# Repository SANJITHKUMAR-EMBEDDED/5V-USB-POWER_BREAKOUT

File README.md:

# USB-C to 3.3V Power Supply

A simple and robust power supply board that takes 5V from any USB-C port and provides a stable 3.3V output. This is **Project 1** of my #50BoardChallenge to become a job-ready PCB design engineer.

## Features
* USB-C Power Input
* 3.3V LDO Regulator (AP2112K)
* Header pin outputs for both 5V and 3.3V
* 4x 3mm Mounting Holes for stable mounting

## Professional Design Rules
This board was designed using a professional workflow in KiCad:
* **Solid `GND` Plane:** Used a solid copper pour on the bottom layer for low noise and a stable return path.
* **Power Traces:** Used KiCad's **Net Classes** to define wide `20mil` traces for the `+5V`, `+3.3V`, and `GND` nets.
* **Decoupling:** Placed input and output capacitors as close as possible to the regulator for stability.
* **DRC:** The final design passed all Design Rules Checks with **0 errors and 0 warnings**.

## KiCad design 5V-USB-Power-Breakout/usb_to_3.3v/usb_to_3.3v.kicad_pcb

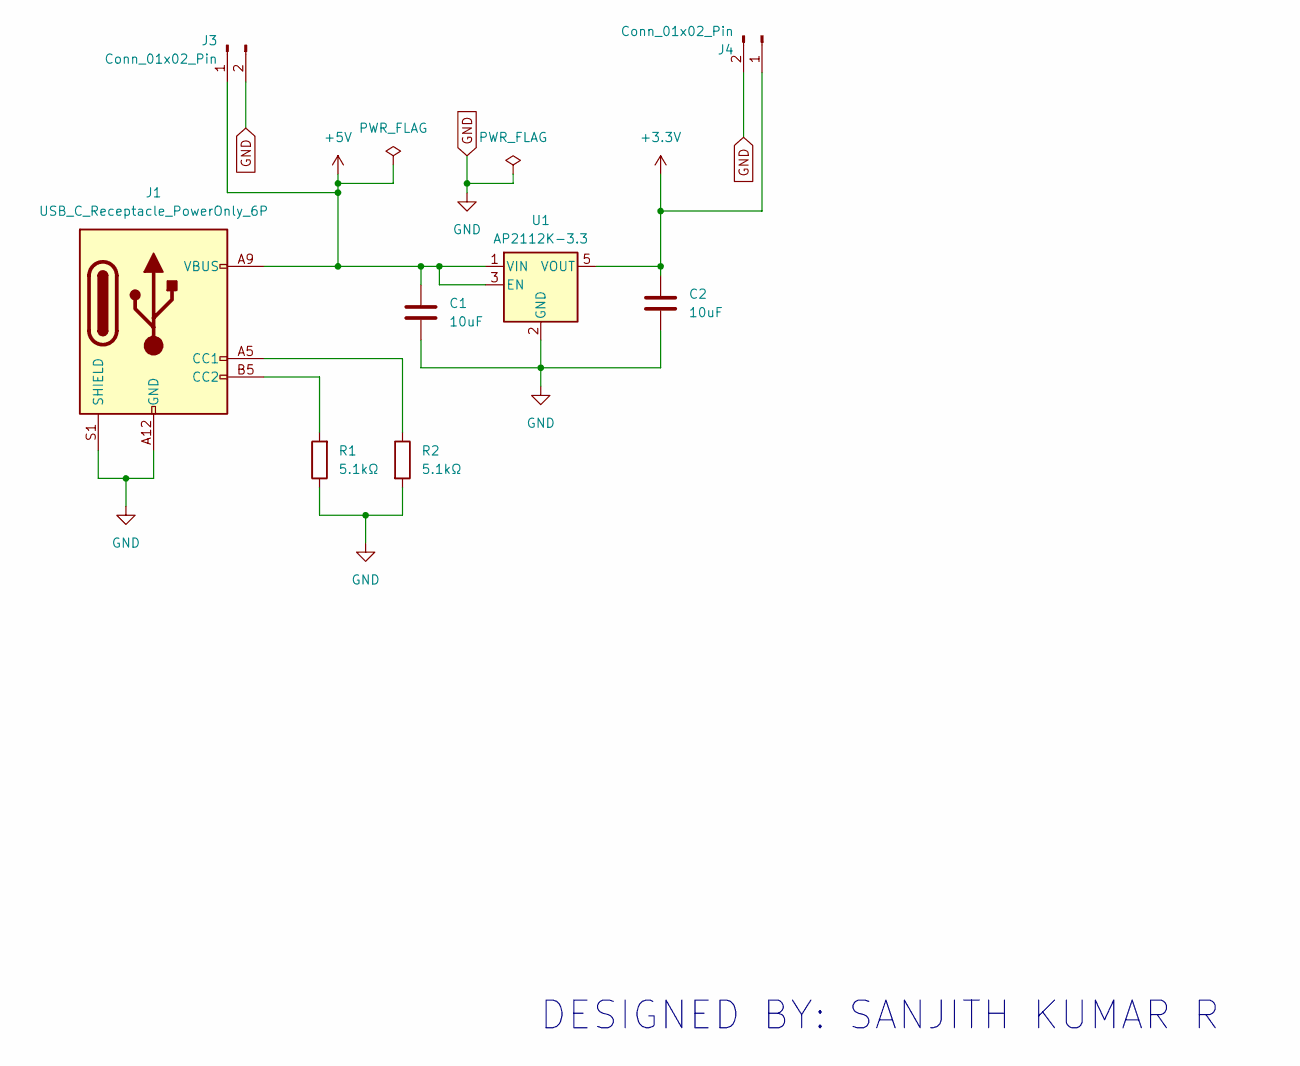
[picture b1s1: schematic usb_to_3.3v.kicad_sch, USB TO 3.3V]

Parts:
C1, C2: 10uF; C_0805_2012Metric
J1: USB_C_Receptacle_PowerOnly_6P; USB_C_Receptacle_GCT_USB4135-GF-A_6P_TopMnt_Horizontal
J3, J4: Conn_01x02_Pin; PinHeader_1x02_P2.54mm_Vertical
R1, R2: 5.1kΩ; R_0805_2012Metric
U1: AP2112K-3.3; SOT-23-5

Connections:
+3.3V: C2.1, J4.1, U1.5 (VOUT)
+5V: C1.1, J1.A9 (VBUS), J1.B9 (VBUS), J3.1, U1.1 (VIN), U1.3 (EN)
GND: C1.2, C2.2, J1.A12 (GND), J1.B12 (GND), J1.S1 (SHIELD), J3.2, J4.2, R1.1, R2.2, U1.2 (GND)
unnamed: J1.A5 (CC1), R2.1
unnamed: J1.B5 (CC2), R1.2

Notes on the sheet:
DESIGNED BY: SANJITH KUMAR R

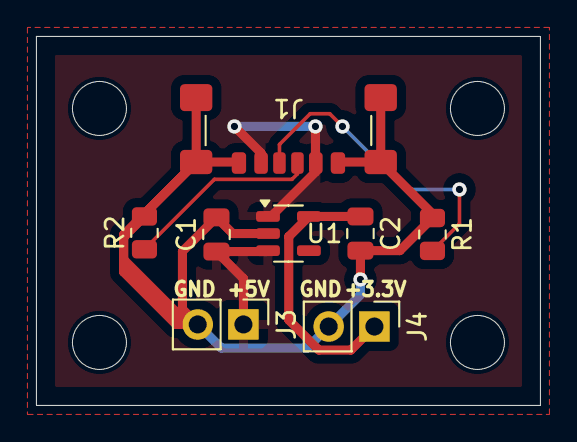
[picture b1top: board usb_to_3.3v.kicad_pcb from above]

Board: 2 copper layers, 28.0 x 20.5 mm, 8 parts (0 on the bottom side), 5 nets.

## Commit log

2025-10-30 First PCB project upload
2025-10-30 Add README for USB-C to 3.3V Power Supply project
    Added a README file for the USB-C to 3.3V power supply project, detailing features and design rules.
2025-10-30 added README
    Removed image reference from README.
2025-10-31 Create 3D_RENDERS
